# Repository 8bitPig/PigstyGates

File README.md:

# PigstyGates
teensy based USB-Midi to 24 Jack Gate Out

cc-by-nc-sa 4.0

v1:
Prototype failed! 
After about 2 weeks I stumbled upon the difference between the 74HC595 and 74HCT595.
Next Order will contain a 74HCT595 for retesting. 
Actually I have to guess, that the communication input levels are not enough for the 74HC595.
If this is not the Problem, I will retry with a line driver. 
v1 is still interesting for those who want a minimum part count and 0-5V Output levels. 
v1 code is still to do. Testcode is done and should work. To be shared after testing. 

v2:
-better layout
-correct part names and values
-got rid of SPI / using all 24 GPIO of the small size teensy boards
- TESTED AND WORKING :)
- ebay ADUM3160 USB Isolator since today was only working in theory. <- PROOVED!!!! :) 
- I sent in a sequence with 50% pulse cycle and 1/128 notes at a speed of 120 BPM in all 24 notes simultanously for testing without laggs on a teensy LC.
- code can't be simpler I guess. ^^

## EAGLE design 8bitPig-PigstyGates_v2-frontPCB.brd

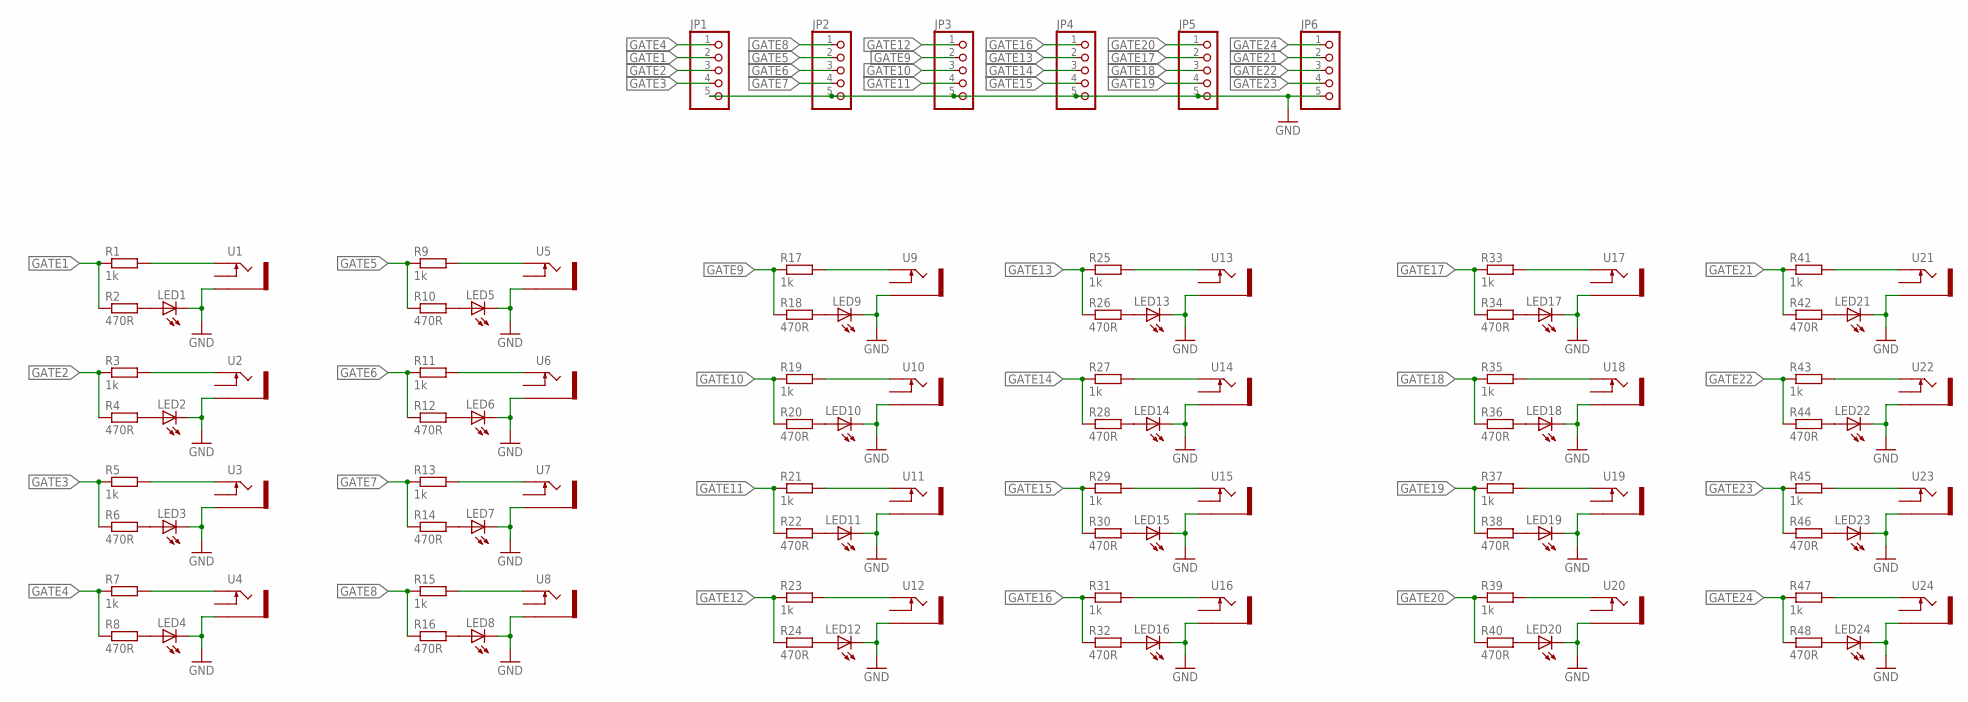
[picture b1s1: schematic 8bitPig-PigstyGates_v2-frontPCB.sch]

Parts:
JP1, JP2, JP3, JP4, JP5, JP6: PINHD-1X5; 1X05
LED1, LED2, LED3, LED4, LED5, LED6, LED7, LED8, LED9, LED10, LED11, LED12, LED13, LED14, LED15, LED16, LED17, LED18, LED19, LED20, LED21, LED22, LED23, LED24: LED3MM
R1, R3, R5, R7, R9, R11, R13, R15, R17, R19, R21, R23, R25, R27, R29, R31, R33, R35, R37, R39, R41, R43, R45, R47: 1k; R0603
R2, R4, R6, R8, R10, R12, R14, R16, R18, R20, R22, R24, R26, R28, R30, R32, R34, R36, R38, R40, R42, R44, R46, R48: 470R; R0603
U1, U2, U3, U4, U5, U6, U7, U8, U9, U10, U11, U12, U13, U14, U15, U16, U17, U18, U19, U20, U21, U22, U23, U24: THONKICONNNEW; WQP-PJ301M-12_JACK

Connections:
GATE1: JP1.2, R1.1, R2.1
GATE2: JP1.3, R3.1, R4.1
GATE3: JP1.4, R5.1, R6.1
GATE4: JP1.1, R7.1, R8.1
GATE5: JP2.2, R9.1, R10.1
GATE6: JP2.3, R11.1, R12.1
GATE7: JP2.4, R13.1, R14.1
GATE8: JP2.1, R15.1, R16.1
GATE9: JP3.2, R17.1, R18.1
GATE10: JP3.3, R19.1, R20.1
GATE11: JP3.4, R21.1, R22.1
GATE12: JP3.1, R23.1, R24.1
GATE13: JP4.2, R25.1, R26.1
GATE14: JP4.3, R27.1, R28.1
GATE15: JP4.4, R29.1, R30.1
GATE16: JP4.1, R31.1, R32.1
GATE17: JP5.2, R33.1, R34.1
GATE18: JP5.3, R35.1, R36.1
GATE19: JP5.4, R37.1, R38.1
GATE20: JP5.1, R39.1, R40.1
GATE21: JP6.2, R41.1, R42.1
GATE22: JP6.3, R43.1, R44.1
GATE23: JP6.4, R45.1, R46.1
GATE24: JP6.1, R47.1, R48.1
GND: JP1.5, JP2.5, JP3.5, JP4.5, JP5.5, JP6.5, LED1.K (C), LED2.K (C), LED3.K (C), LED4.K (C), LED5.K (C), LED6.K (C), LED7.K (C), LED8.K (C), LED9.K (C), LED10.K (C), LED11.K (C), LED12.K (C), LED13.K (C), LED14.K (C), LED15.K (C), LED16.K (C), LED17.K (C), LED18.K (C), LED19.K (C), LED20.K (C), LED21.K (C), LED22.K (C), LED23.K (C), LED24.K (C), U1.P$3_SLEEVE (SLEEVE), U2.P$3_SLEEVE (SLEEVE), U3.P$3_SLEEVE (SLEEVE), U4.P$3_SLEEVE (SLEEVE), U5.P$3_SLEEVE (SLEEVE), U6.P$3_SLEEVE (SLEEVE), U7.P$3_SLEEVE (SLEEVE), U8.P$3_SLEEVE (SLEEVE), U9.P$3_SLEEVE (SLEEVE), U10.P$3_SLEEVE (SLEEVE), U11.P$3_SLEEVE (SLEEVE), U12.P$3_SLEEVE (SLEEVE), U13.P$3_SLEEVE (SLEEVE), U14.P$3_SLEEVE (SLEEVE), U15.P$3_SLEEVE (SLEEVE), U16.P$3_SLEEVE (SLEEVE), U17.P$3_SLEEVE (SLEEVE), U18.P$3_SLEEVE (SLEEVE), U19.P$3_SLEEVE (SLEEVE), U20.P$3_SLEEVE (SLEEVE), U21.P$3_SLEEVE (SLEEVE), U22.P$3_SLEEVE (SLEEVE), U23.P$3_SLEEVE (SLEEVE), U24.P$3_SLEEVE (SLEEVE)
unnamed: LED1.A, R2.2
unnamed: R1.2, U1.P$1_TIP (TIP)
unnamed: LED2.A, R4.2
unnamed: R3.2, U2.P$1_TIP (TIP)
unnamed: LED3.A, R6.2
unnamed: R5.2, U3.P$1_TIP (TIP)
unnamed: LED4.A, R8.2
unnamed: R7.2, U4.P$1_TIP (TIP)
unnamed: LED5.A, R10.2
unnamed: R9.2, U5.P$1_TIP (TIP)
unnamed: LED6.A, R12.2
unnamed: R11.2, U6.P$1_TIP (TIP)
unnamed: LED7.A, R14.2
unnamed: R13.2, U7.P$1_TIP (TIP)
unnamed: LED8.A, R16.2
unnamed: R15.2, U8.P$1_TIP (TIP)
unnamed: LED9.A, R18.2
unnamed: R17.2, U9.P$1_TIP (TIP)
unnamed: LED10.A, R20.2
unnamed: R19.2, U10.P$1_TIP (TIP)
unnamed: LED11.A, R22.2
unnamed: R21.2, U11.P$1_TIP (TIP)
unnamed: LED12.A, R24.2
unnamed: R23.2, U12.P$1_TIP (TIP)
unnamed: LED13.A, R26.2
unnamed: R25.2, U13.P$1_TIP (TIP)
unnamed: LED14.A, R28.2
unnamed: R27.2, U14.P$1_TIP (TIP)
unnamed: LED15.A, R30.2
unnamed: R29.2, U15.P$1_TIP (TIP)
unnamed: LED17.A, R34.2
unnamed: R33.2, U17.P$1_TIP (TIP)
unnamed: LED16.A, R32.2
unnamed: R31.2, U16.P$1_TIP (TIP)
unnamed: LED18.A, R36.2
unnamed: R35.2, U18.P$1_TIP (TIP)
unnamed: LED19.A, R38.2
unnamed: R37.2, U19.P$1_TIP (TIP)
unnamed: LED20.A, R40.2
unnamed: R39.2, U20.P$1_TIP (TIP)
unnamed: LED21.A, R42.2
unnamed: R41.2, U21.P$1_TIP (TIP)
unnamed: LED22.A, R44.2
unnamed: R43.2, U22.P$1_TIP (TIP)
unnamed: LED23.A, R46.2
unnamed: R45.2, U23.P$1_TIP (TIP)
unnamed: LED24.A, R48.2
unnamed: R47.2, U24.P$1_TIP (TIP)

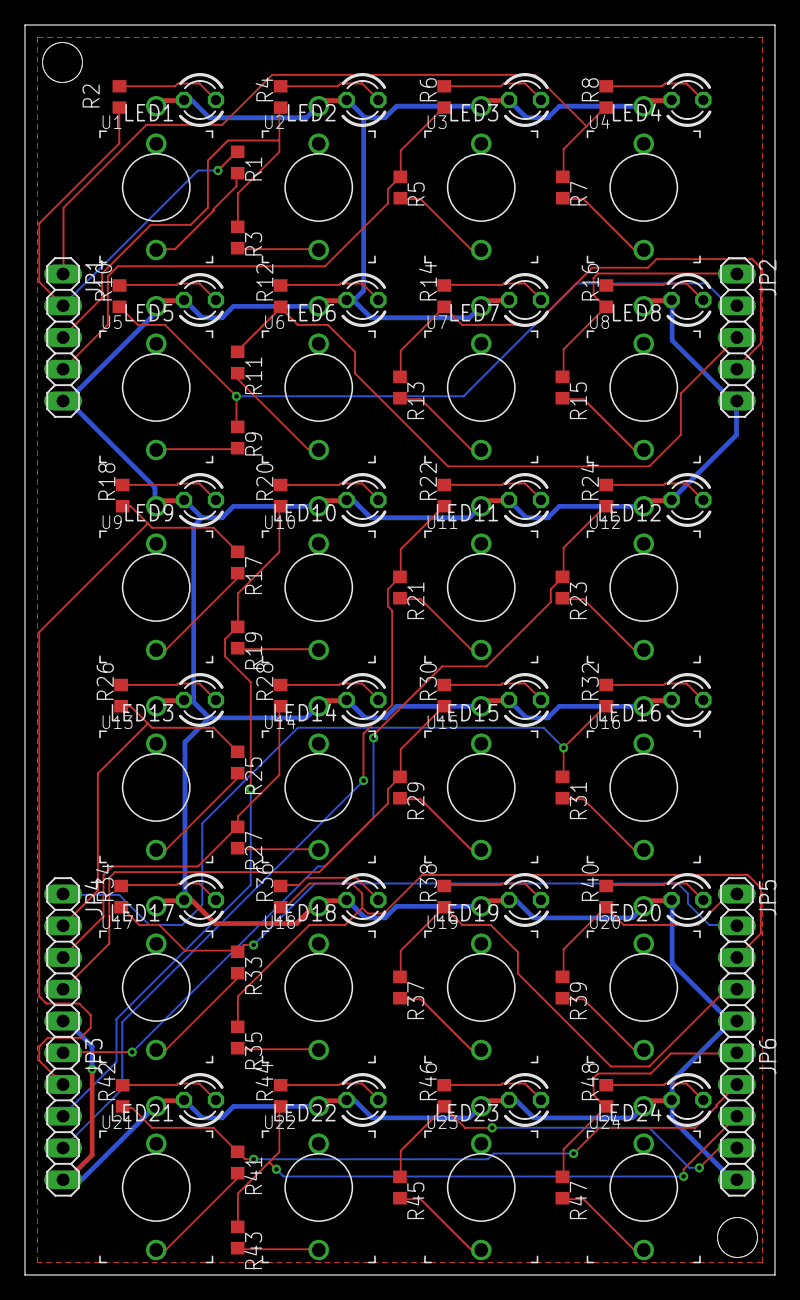
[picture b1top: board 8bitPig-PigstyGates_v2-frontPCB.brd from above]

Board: 2 copper layers, 60.0 x 100.0 mm, 102 parts (0 on the bottom side), 73 nets.

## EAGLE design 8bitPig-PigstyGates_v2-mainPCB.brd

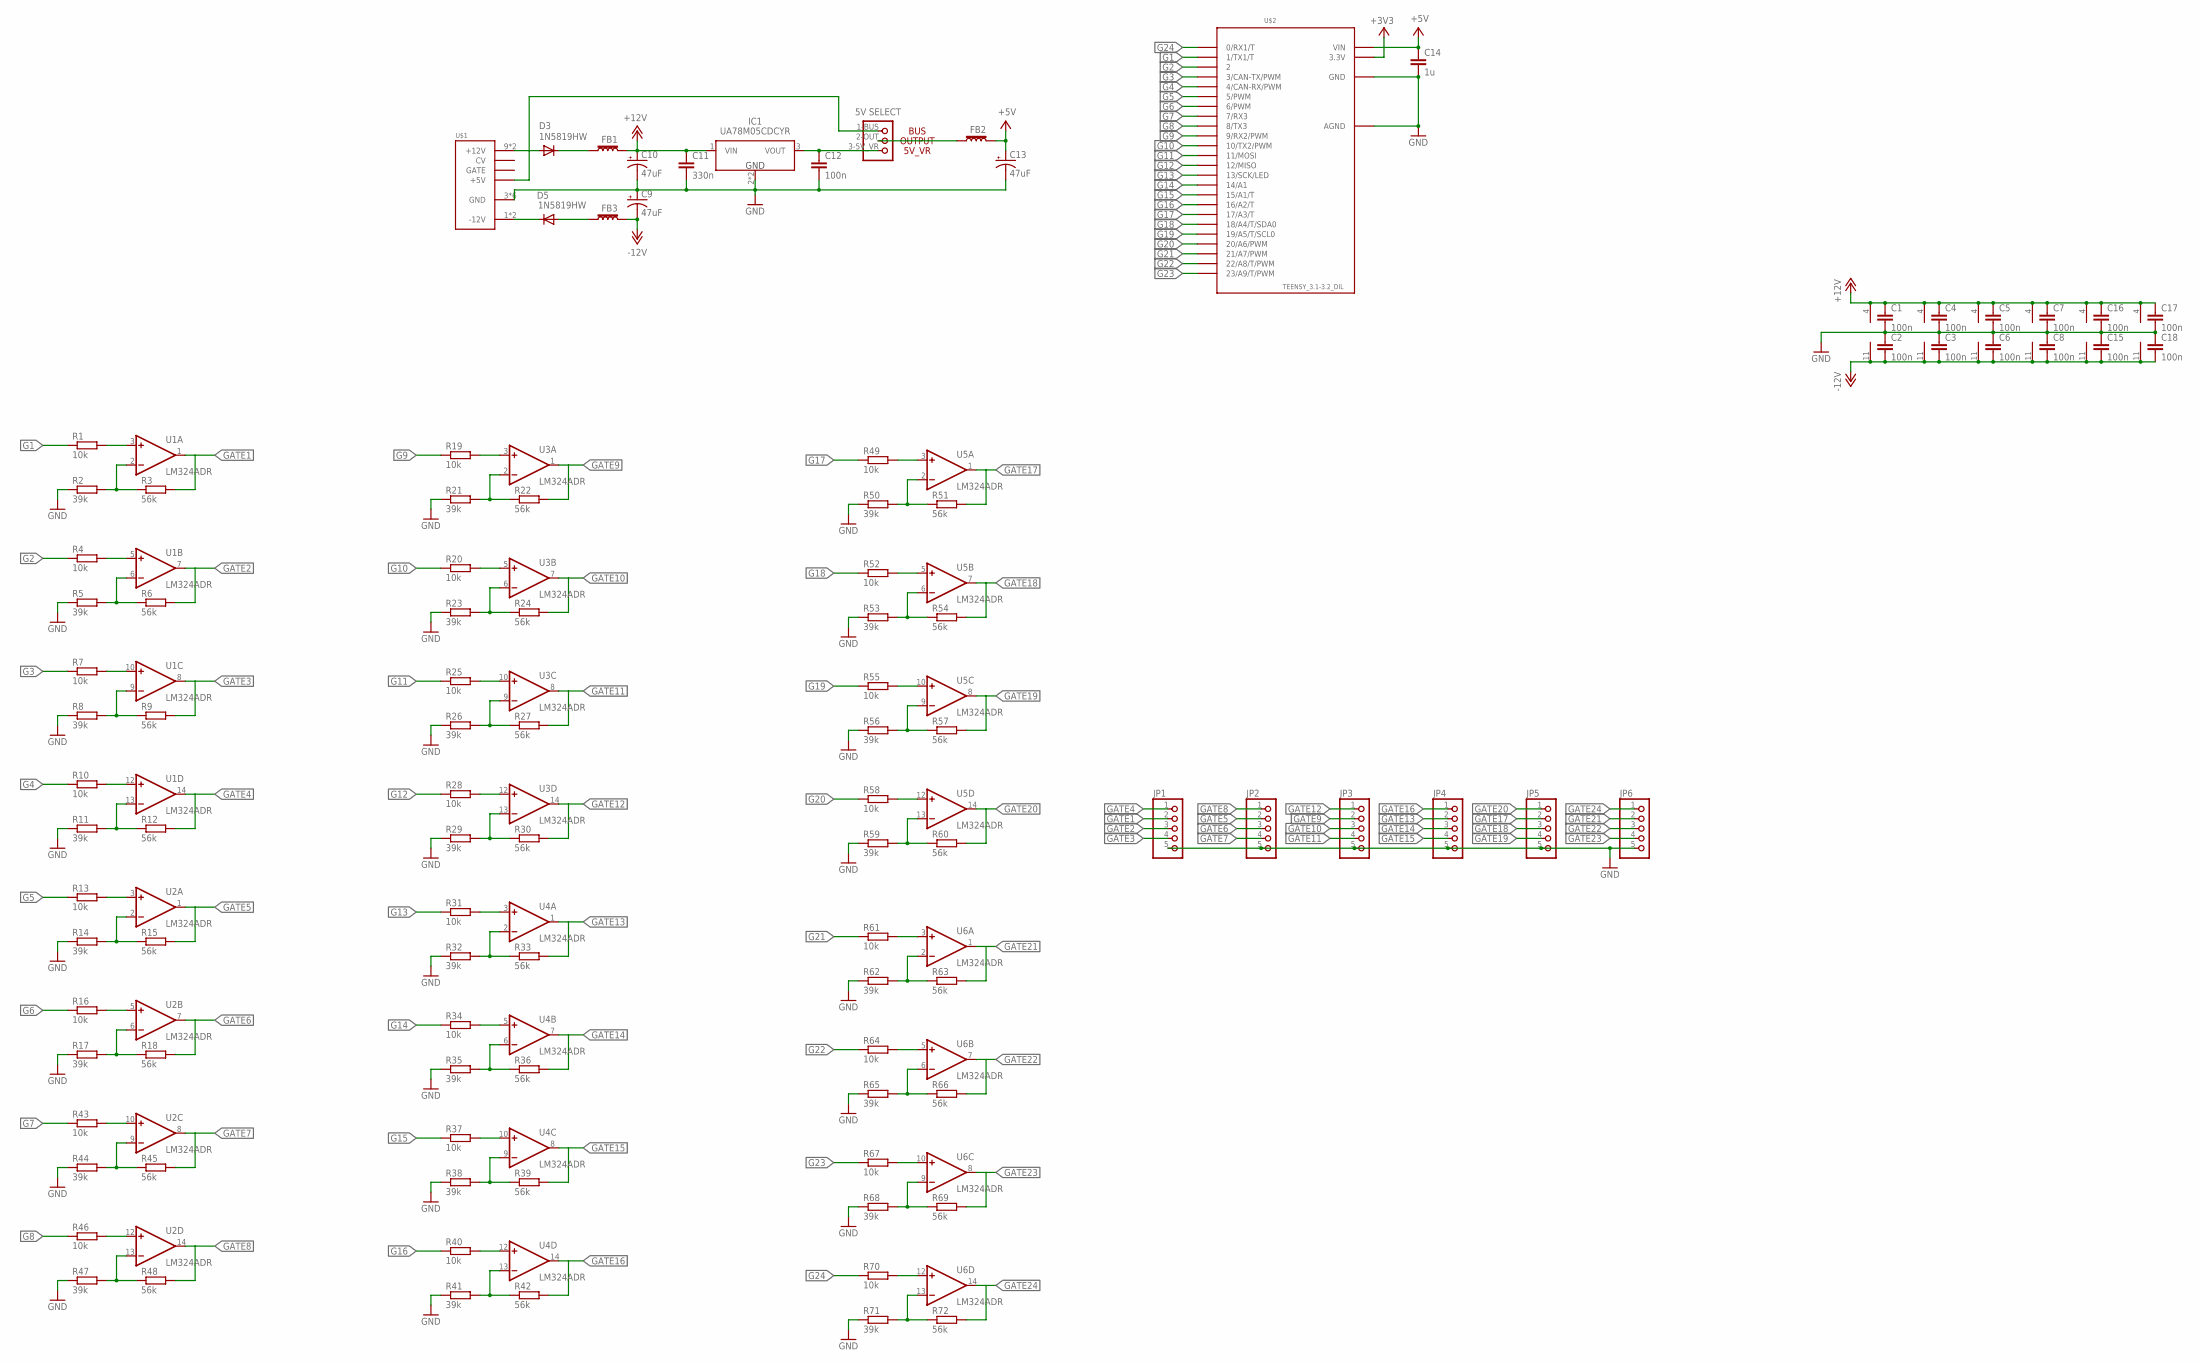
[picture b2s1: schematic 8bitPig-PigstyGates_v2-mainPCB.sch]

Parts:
C1, C2, C3, C4, C5, C6, C7, C8, C12, C15, C16, C17, C18: 100n; C0603
C9, C10, C13: 47uF; PANASONIC_D
C11: 330n; C0603
C14: 1u; C0603
D3, D5: 1N5819HW; DIODE_SOD123
FB1, FB2, FB3: 30Ω/1.8A; 0603
IC1: UA78M05CDCYR; SOT230P700X180-4N
JP1, JP2, JP3, JP4, JP5, JP6: PINHD-1X5; 1X05
JP_5V: SELECTOR_POWER
R1, R4, R7, R10, R13, R16, R19, R20, R25, R28, R31, R34, R37, R40, R43, R46, R49, R52, R55, R58, R61, R64, R67, R70: 10k; R0603
R2, R5, R8, R11, R14, R17, R21, R23, R26, R29, R32, R35, R38, R41, R44, R47, R50, R53, R56, R59, R62, R65, R68, R71: 39k; R0603
R3, R6, R9, R12, R15, R18, R22, R24, R27, R30, R33, R36, R39, R42, R45, R48, R51, R54, R57, R60, R63, R66, R69, R72: 56k; R0603
U1, U2, U3, U4, U5, U6: LM324ADR; SO14
U$1: POWER; POWER_16
U$2: TEENSY_3.1-3.2_DIL; TEENSY_3.0-3.2&LC_DIL

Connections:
+3V3: U$2.3.3V
+5V: C13.+, C14.1, FB2.2, U$2.VIN
+12V: C1.1, C4.1, C5.1, C7.1, C10.+, C11.1, C16.1, C17.1, FB1.2, IC1.1 (VIN), U1.4 (V+), U2.4 (V+), U3.4 (V+), U4.4 (V+), U5.4 (V+), U6.4 (V+)
-12V: C2.2, C3.2, C6.2, C8.2, C9.-, C15.2, C18.2, FB3.2, U1.11 (V-), U2.11 (V-), U3.11 (V-), U4.11 (V-), U5.11 (V-), U6.11 (V-)
G1: R1.1, U$2.1 (1/TX1/T)
G2: R4.1, U$2.2
G3: R7.1, U$2.3 (3/CAN-TX/PWM)
G4: R10.1, U$2.4 (4/CAN-RX/PWM)
G5: R13.1, U$2.5 (5/PWM)
G6: R16.1, U$2.6 (6/PWM)
G7: R43.1, U$2.7 (7/RX3)
G8: R46.1, U$2.8 (8/TX3)
G9: R19.1, U$2.9 (9/RX2/PWM)
G10: R20.1, U$2.10 (10/TX2/PWM)
G11: R25.1, U$2.11 (11/MOSI)
G12: R28.1, U$2.12 (12/MISO)
G13: R31.1, U$2.13 (13/SCK/LED)
G14: R34.1, U$2.14/A0 (14/A1)
G15: R37.1, U$2.15/A1 (15/A1/T)
G16: R40.1, U$2.16/A2 (16/A2/T)
G17: R49.1, U$2.17/A3 (17/A3/T)
G18: R52.1, U$2.18/A4 (18/A4/T/SDA0)
G19: R55.1, U$2.19/A5 (19/A5/T/SCL0)
G20: R58.1, U$2.20/A6 (20/A6/PWM)
G21: R61.1, U$2.21/A7 (21/A7/PWM)
G22: R64.1, U$2.22/A8 (22/A8/T/PWM)
G23: R67.1, U$2.23/A9 (23/A9/T/PWM)
G24: R70.1, U$2.0 (0/RX1/T)
GATE1: JP1.2, R3.2, U1.1 (OUT)
GATE2: JP1.3, R6.2, U1.7 (OUT)
GATE3: JP1.4, R9.2, U1.8 (OUT)
GATE4: JP1.1, R12.2, U1.14 (OUT)
GATE5: JP2.2, R15.2, U2.1 (OUT)
GATE6: JP2.3, R18.2, U2.7 (OUT)
GATE7: JP2.4, R45.2, U2.8 (OUT)
GATE8: JP2.1, R48.2, U2.14 (OUT)
GATE9: JP3.2, R22.2, U3.1 (OUT)
GATE10: JP3.3, R24.2, U3.7 (OUT)
GATE11: JP3.4, R27.2, U3.8 (OUT)
GATE12: JP3.1, R30.2, U3.14 (OUT)
GATE13: JP4.2, R33.2, U4.1 (OUT)
GATE14: JP4.3, R36.2, U4.7 (OUT)
GATE15: JP4.4, R39.2, U4.8 (OUT)
GATE16: JP4.1, R42.2, U4.14 (OUT)
GATE17: JP5.2, R51.2, U5.1 (OUT)
GATE18: JP5.3, R54.2, U5.7 (OUT)
GATE19: JP5.4, R57.2, U5.8 (OUT)
GATE20: JP5.1, R60.2, U5.14 (OUT)
GATE21: JP6.2, R63.2, U6.1 (OUT)
GATE22: JP6.3, R66.2, U6.7 (OUT)
GATE23: JP6.4, R69.2, U6.8 (OUT)
GATE24: JP6.1, R72.2, U6.14 (OUT)
GND: C1.2, C2.1, C3.1, C4.2, C5.2, C6.1, C7.2, C8.1, C9.+, C10.-, C11.2, C12.2, C13.-, C14.2, C15.1, C16.2, C17.2, C18.1, IC1.2 (GND), IC1.4 (GND), JP1.5, JP2.5, JP3.5, JP4.5, JP5.5, JP6.5, R2.1, R5.1, R8.1, R11.1, R14.1, R17.1, R21.1, R23.1, R26.1, R29.1, R32.1, R35.1, R38.1, R41.1, R44.1, R47.1, R50.1, R53.1, R56.1, R59.1, R62.1, R65.1, R68.1, R71.1, U$1.3 (GND), U$1.4 (GND), U$1.5 (GND), U$1.6 (GND), U$1.7 (GND), U$1.8 (GND), U$2.AGND, U$2.GND
unnamed: R1.2, U1.3 (+IN)
unnamed: R2.2, R3.1, U1.2 (-IN)
unnamed: R4.2, U1.5 (+IN)
unnamed: R5.2, R6.1, U1.6 (-IN)
unnamed: R7.2, U1.10 (+IN)
unnamed: R8.2, R9.1, U1.9 (-IN)
unnamed: R10.2, U1.12 (+IN)
unnamed: R11.2, R12.1, U1.13 (-IN)
unnamed: D3.A, U$1.9 (+12V), U$1.10 (+12V)
unnamed: D5.C, U$1.1 (-12V), U$1.2 (-12V)
unnamed: D5.A, FB3.1
unnamed: D3.C, FB1.1
unnamed: JP_5V.1-BUS, U$1.11 (+5V), U$1.12 (+5V)
unnamed: C12.1, IC1.3 (VOUT), JP_5V.3-5V_VR (3-VR)
unnamed: FB2.1, JP_5V.2-OUT
unnamed: R13.2, U2.3 (+IN)
unnamed: R19.2, U3.3 (+IN)
unnamed: R20.2, U3.5 (+IN)
unnamed: R21.2, R22.1, U3.2 (-IN)
unnamed: R23.2, R24.1, U3.6 (-IN)
unnamed: R25.2, U3.10 (+IN)
unnamed: R26.2, R27.1, U3.9 (-IN)
unnamed: R28.2, U3.12 (+IN)
unnamed: R29.2, R30.1, U3.13 (-IN)
unnamed: R31.2, U4.3 (+IN)
unnamed: R32.2, R33.1, U4.2 (-IN)
unnamed: R34.2, U4.5 (+IN)
unnamed: R35.2, R36.1, U4.6 (-IN)
unnamed: R37.2, U4.10 (+IN)
unnamed: R38.2, R39.1, U4.9 (-IN)
unnamed: R40.2, U4.12 (+IN)
unnamed: R41.2, R42.1, U4.13 (-IN)
unnamed: R14.2, R15.1, U2.2 (-IN)
unnamed: R16.2, U2.5 (+IN)
unnamed: R17.2, R18.1, U2.6 (-IN)
unnamed: R43.2, U2.10 (+IN)
unnamed: R44.2, R45.1, U2.9 (-IN)
unnamed: R46.2, U2.12 (+IN)
unnamed: R47.2, R48.1, U2.13 (-IN)
unnamed: R49.2, U5.3 (+IN)
unnamed: R50.2, R51.1, U5.2 (-IN)
unnamed: R52.2, U5.5 (+IN)
unnamed: R53.2, R54.1, U5.6 (-IN)
unnamed: R55.2, U5.10 (+IN)
unnamed: R56.2, R57.1, U5.9 (-IN)
unnamed: R58.2, U5.12 (+IN)
unnamed: R59.2, R60.1, U5.13 (-IN)
unnamed: R61.2, U6.3 (+IN)
unnamed: R62.2, R63.1, U6.2 (-IN)
unnamed: R64.2, U6.5 (+IN)
unnamed: R65.2, R66.1, U6.6 (-IN)
unnamed: R67.2, U6.10 (+IN)
unnamed: R68.2, R69.1, U6.9 (-IN)
unnamed: R70.2, U6.12 (+IN)
unnamed: R71.2, R72.1, U6.13 (-IN)

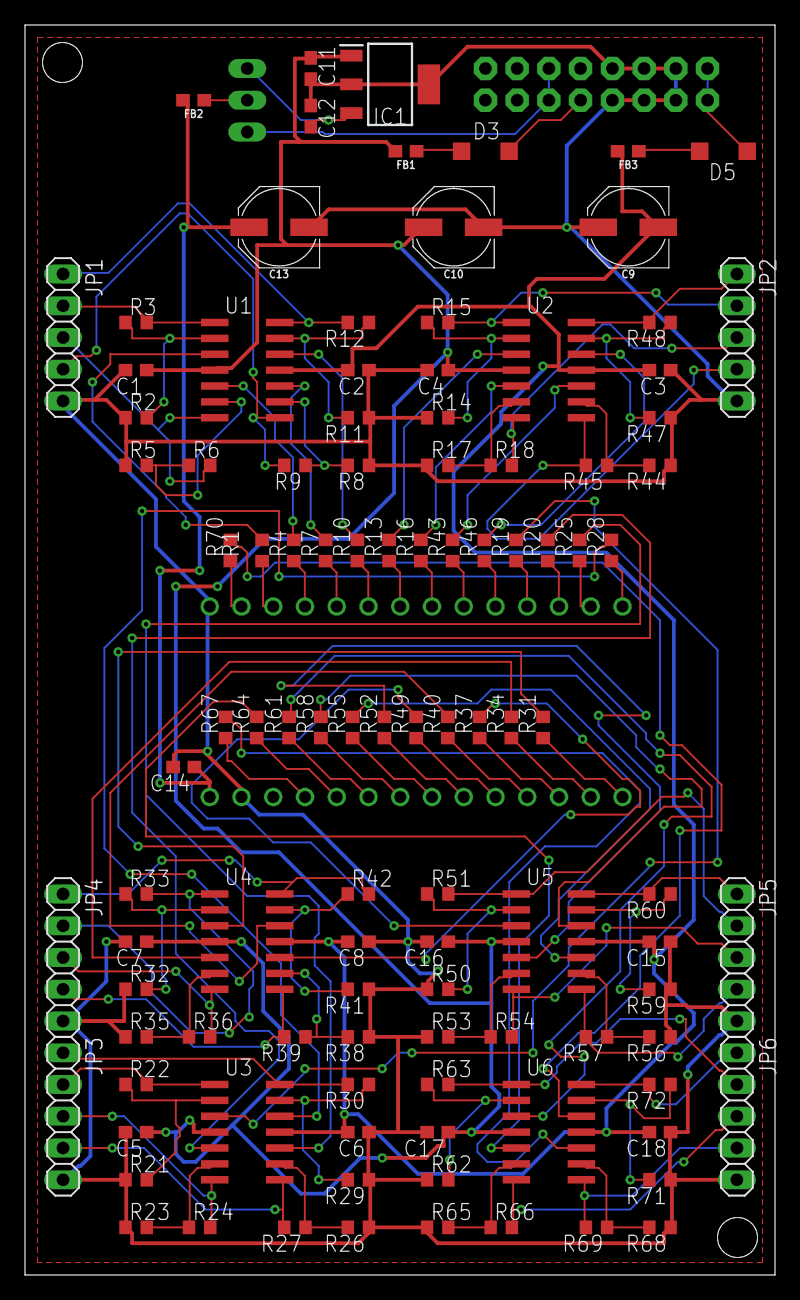
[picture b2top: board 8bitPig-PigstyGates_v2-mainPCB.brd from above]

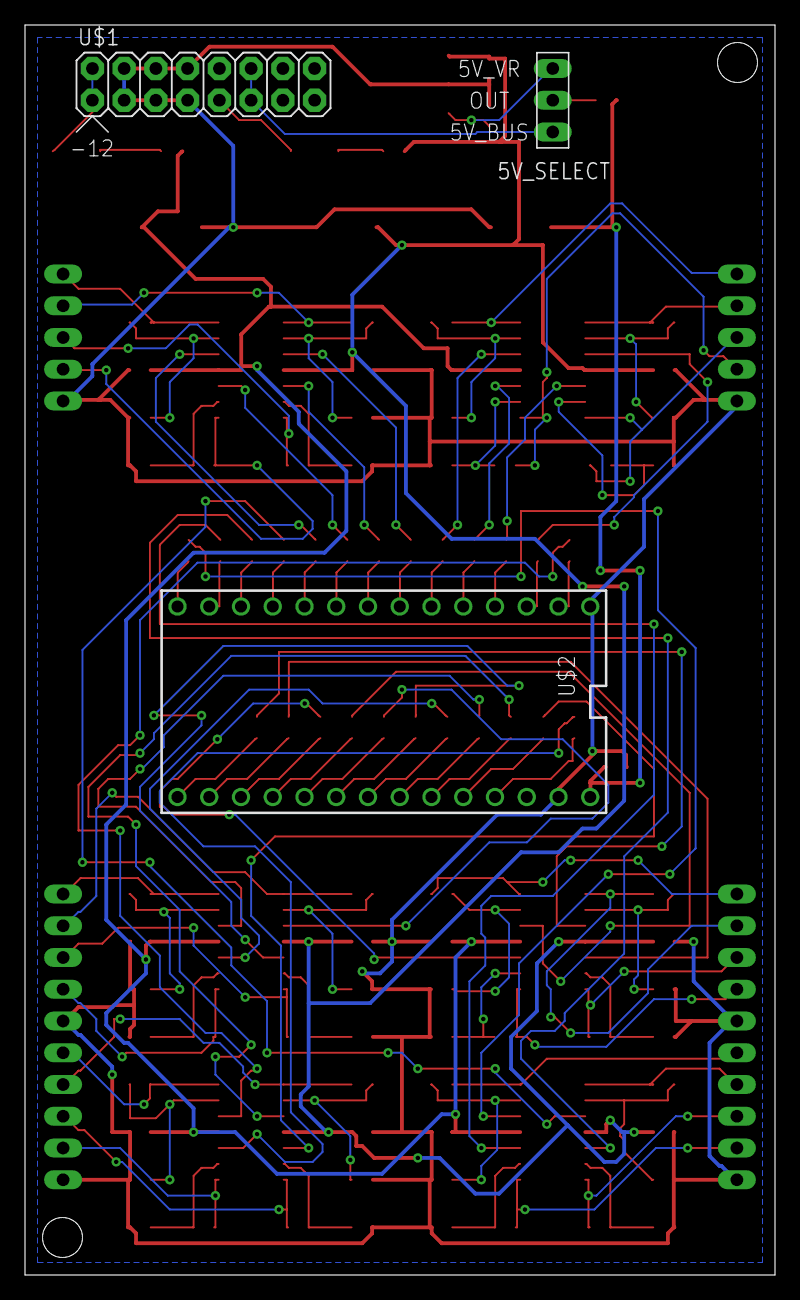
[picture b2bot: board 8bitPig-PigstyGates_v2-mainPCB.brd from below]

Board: 2 copper layers, 60.0 x 100.0 mm, 111 parts (3 on the bottom side), 107 nets.

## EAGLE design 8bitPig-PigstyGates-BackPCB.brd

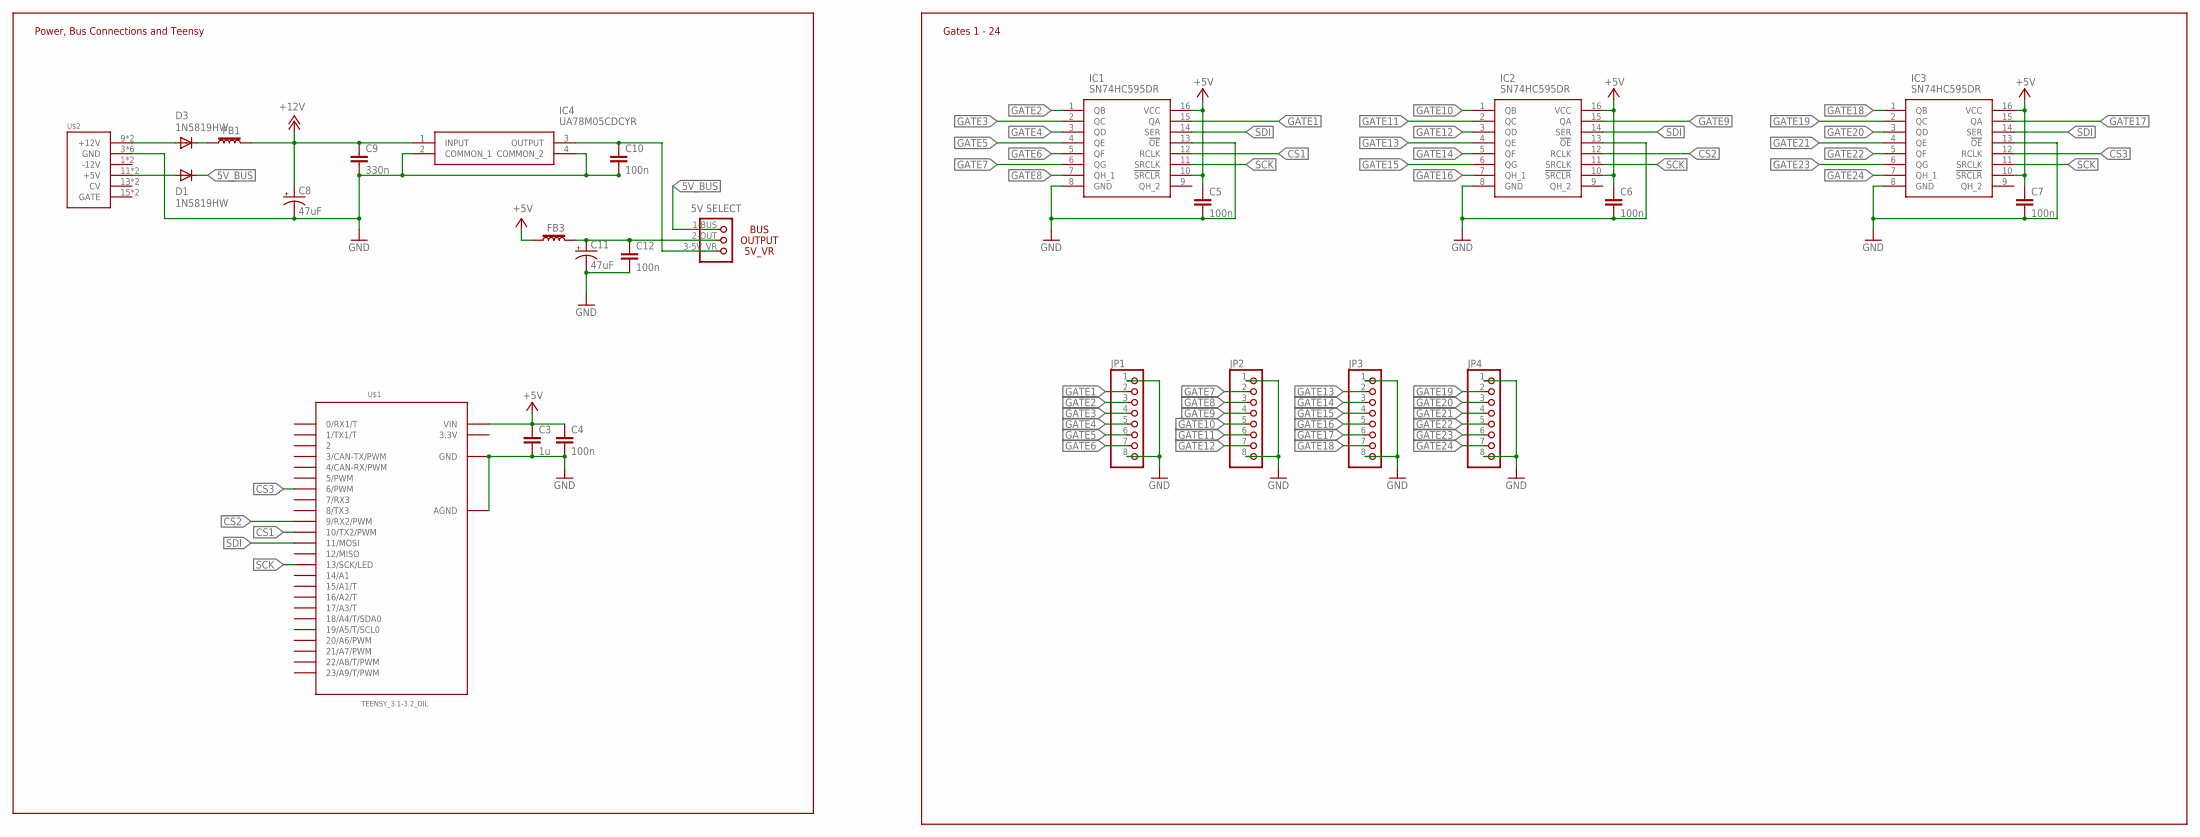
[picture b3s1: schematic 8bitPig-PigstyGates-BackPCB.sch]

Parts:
C3: 1u; C0603
C4, C5, C6, C7, C10, C12: 100n; C0603
C8, C11: 47uF; PANASONIC_D
C9: 330n; C0603
D1, D3: 1N5819HW; DIODE_SOD123
FB1, FB3: 30Ω/1.8A; 0603
IC1, IC2, IC3: SN74HC595DR; SOIC127P600X175-16N
IC4: UA78M05CDCYR; SOT230P700X180-4N
JP1, JP2, JP3, JP4: PINHD-1X8; 1X08
JP5: SELECTOR_POWER
U$1: TEENSY_3.1-3.2_DIL; TEENSY_3.0-3.2&LC_DIL
U$2: POWER; POWER_16

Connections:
3.3V: U$1.3.3V
5V_BUS: D1.C, JP5.1-BUS
+5V: C3.1, C4.1, C5.1, C6.1, C7.1, FB3.1, IC1.10 (!SRCLR), IC1.16 (VCC), IC2.10 (!SRCLR), IC2.16 (VCC), IC3.10 (!SRCLR), IC3.16 (VCC), U$1.VIN
+12V: C8.+, C9.1, FB1.2, IC4.1 (INPUT)
CS1: IC1.12 (RCLK), U$1.10 (10/TX2/PWM)
CS2: IC2.12 (RCLK), U$1.9 (9/RX2/PWM)
CS3: IC3.12 (RCLK), U$1.6 (6/PWM)
GATE1: IC1.15 (QA), JP1.2
GATE2: IC1.1 (QB), JP1.3
GATE3: IC1.2 (QC), JP1.4
GATE4: IC1.3 (QD), JP1.5
GATE5: IC1.4 (QE), JP1.6
GATE6: IC1.5 (QF), JP1.7
GATE7: IC1.6 (QG), JP2.2
GATE8: IC1.7 (QH_1), JP2.3
GATE9: IC2.15 (QA), JP2.4
GATE10: IC2.1 (QB), JP2.5
GATE11: IC2.2 (QC), JP2.6
GATE12: IC2.3 (QD), JP2.7
GATE13: IC2.4 (QE), JP3.2
GATE14: IC2.5 (QF), JP3.3
GATE15: IC2.6 (QG), JP3.4
GATE16: IC2.7 (QH_1), JP3.5
GATE17: IC3.15 (QA), JP3.6
GATE18: IC3.1 (QB), JP3.7
GATE19: IC3.2 (QC), JP4.2
GATE20: IC3.3 (QD), JP4.3
GATE21: IC3.4 (QE), JP4.4
GATE22: IC3.5 (QF), JP4.5
GATE23: IC3.6 (QG), JP4.6
GATE24: IC3.7 (QH_1), JP4.7
GND: C3.2, C4.2, C5.2, C6.2, C7.2, C8.-, C9.2, C10.2, C11.-, C12.2, IC1.8 (GND), IC1.13 (!OE), IC2.8 (GND), IC2.13 (!OE), IC3.8 (GND), IC3.13 (!OE), IC4.2 (COMMON_1), IC4.4 (COMMON_2), JP1.1, JP1.8, JP2.1, JP2.8, JP3.1, JP3.8, JP4.1, JP4.8, U$1.AGND, U$1.GND, U$2.3 (GND), U$2.4 (GND), U$2.5 (GND), U$2.6 (GND), U$2.7 (GND), U$2.8 (GND)
unnamed: D3.A, U$2.9 (+12V), U$2.10 (+12V)
unnamed: D1.A, U$2.11 (+5V), U$2.12 (+5V)
unnamed: C11.+, C12.1, FB3.2, JP5.2-OUT
unnamed: D3.C, FB1.1
unnamed: C10.1, IC4.3 (OUTPUT), JP5.3-5V_VR (3-VR)
SCK: IC1.11 (SRCLK), IC2.11 (SRCLK), IC3.11 (SRCLK), U$1.13 (13/SCK/LED)
SDI: IC1.14 (SER), IC2.14 (SER), IC3.14 (SER), U$1.11 (11/MOSI)

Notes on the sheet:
Gates 1 - 24
Power, Bus Connections and Teensy

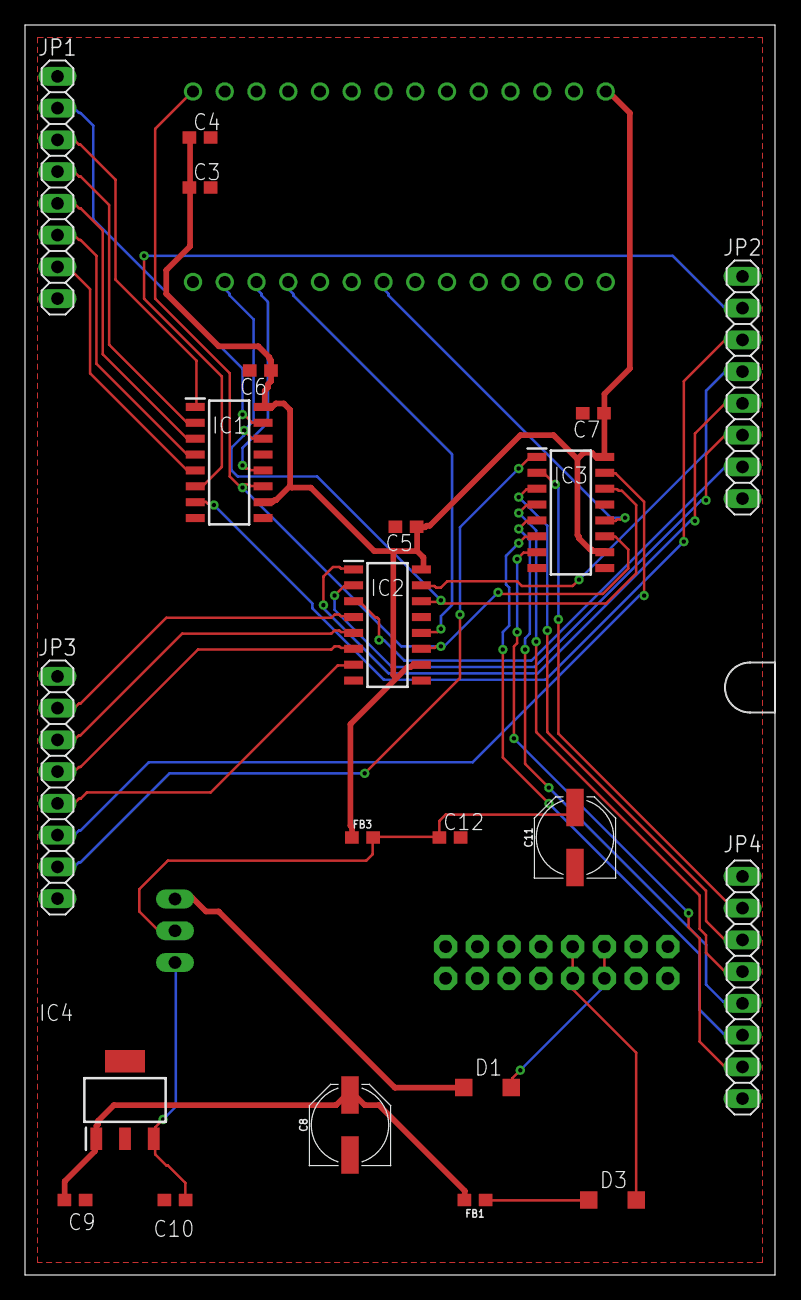
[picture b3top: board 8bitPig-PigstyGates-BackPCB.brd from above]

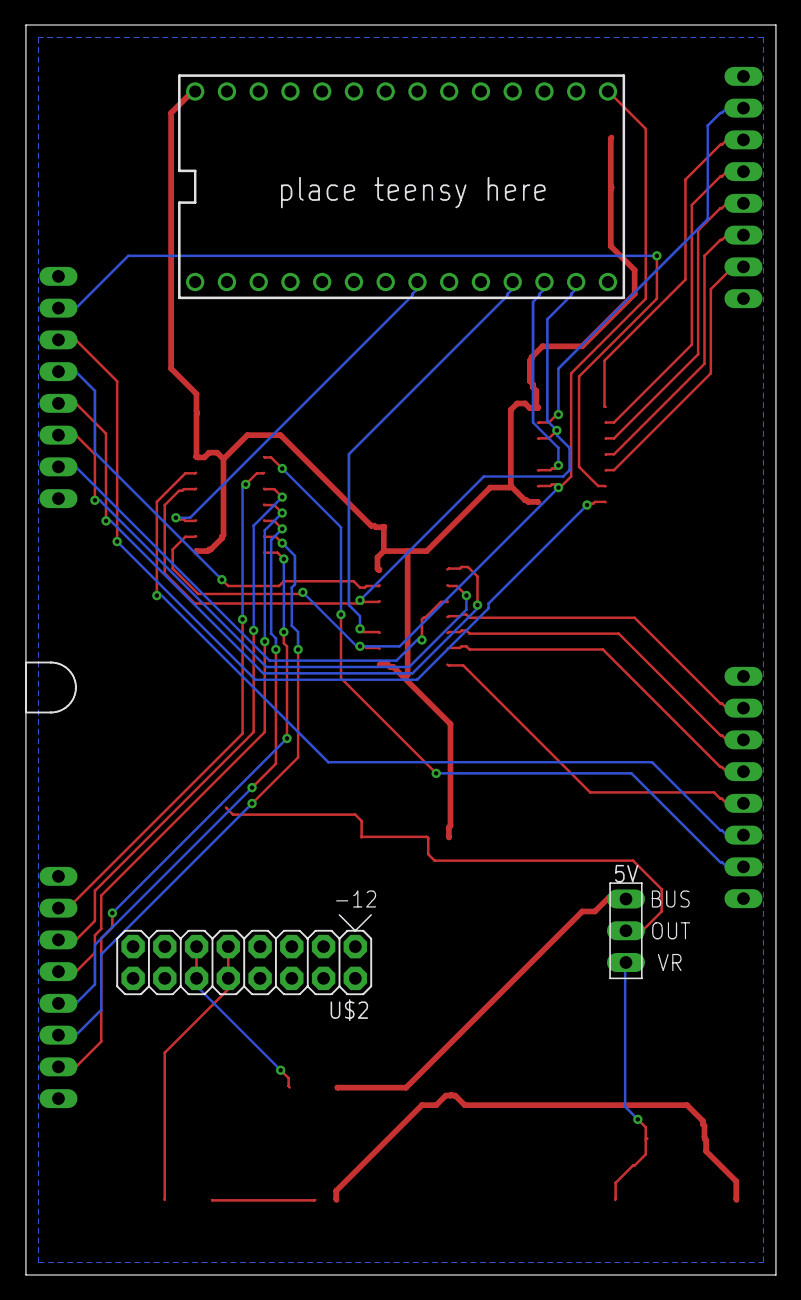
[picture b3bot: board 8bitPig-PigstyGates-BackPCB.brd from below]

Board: 2 copper layers, 59.9 x 99.8 mm, 26 parts (3 on the bottom side), 38 nets.

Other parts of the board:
U$3: PANEL_CABLE_CUTOUT

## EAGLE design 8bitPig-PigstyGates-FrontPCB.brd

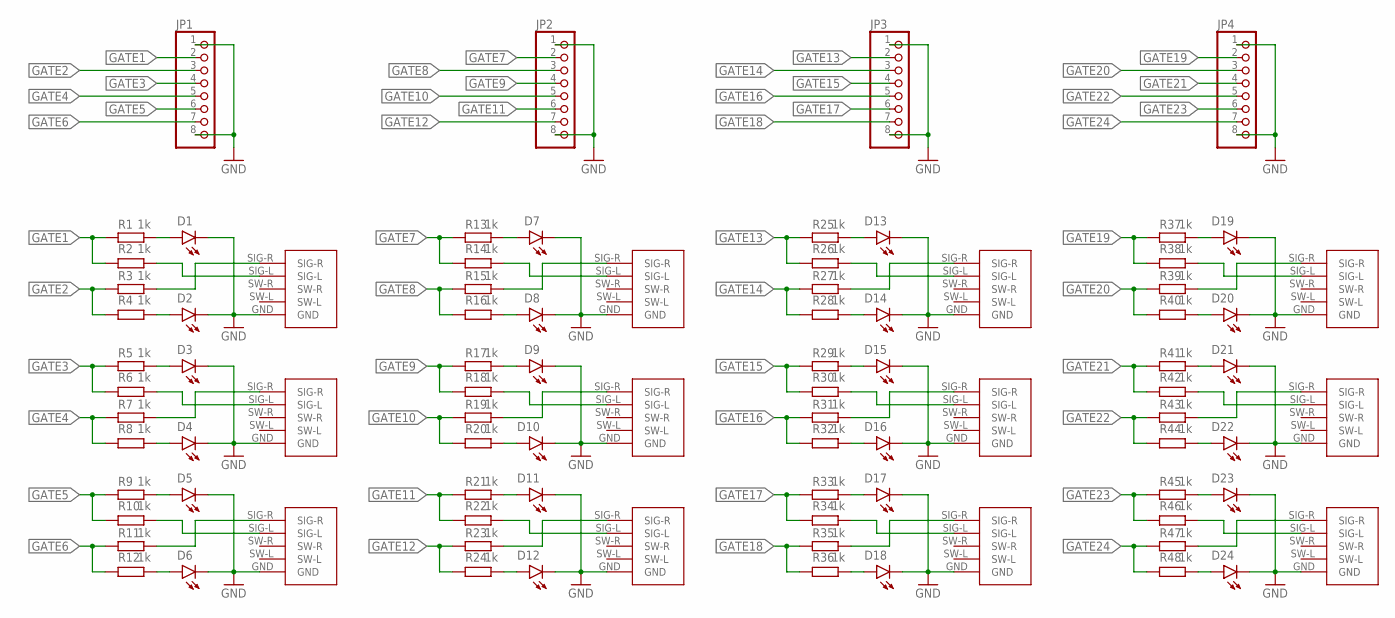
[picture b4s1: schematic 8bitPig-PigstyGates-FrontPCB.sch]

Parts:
D1, D2, D3, D4, D5, D6, D7, D8, D9, D10, D11, D12, D13, D14, D15, D16, D17, D18, D19, D20, D21, D22, D23, D24: LED3MM; LED_3MM
DUAL_JACK_1, DUAL_JACK_2, DUAL_JACK_3, DUAL_JACK_4, DUAL_JACK_5, DUAL_JACK_6, DUAL_JACK_7, DUAL_JACK_8, DUAL_JACK_9, DUAL_JACK_10, DUAL_JACK_11, DUAL_JACK_12: DUAL_MONO_THONKICONN; DUAL_THONKICONN_MONO
JP1, JP2, JP3, JP4: PINHD-1X8; 1X08
R1, R2, R3, R4, R5, R6, R7, R8, R9, R10, R11, R12, R13, R14, R15, R16, R17, R18, R19, R20, R21, R22, R23, R24, R25, R26, R27, R28, R29, R30, R31, R32, R33, R34, R35, R36, R37, R38, R39, R40, R41, R42, R43, R44, R45, R46, R47, R48: 1k; R0603

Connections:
GATE1: JP1.2, R1.1, R2.1
GATE2: JP1.3, R3.1, R4.1
GATE3: JP1.4, R5.1, R6.1
GATE4: JP1.5, R7.1, R8.1
GATE5: JP1.6, R9.1, R10.1
GATE6: JP1.7, R11.1, R12.1
GATE7: JP2.2, R13.1, R14.1
GATE8: JP2.3, R15.1, R16.1
GATE9: JP2.4, R17.1, R18.1
GATE10: JP2.5, R19.1, R20.1
GATE11: JP2.6, R21.1, R22.1
GATE12: JP2.7, R23.1, R24.1
GATE13: JP3.2, R25.1, R26.1
GATE14: JP3.3, R27.1, R28.1
GATE15: JP3.4, R29.1, R30.1
GATE16: JP3.5, R31.1, R32.1
GATE17: JP3.6, R33.1, R34.1
GATE18: JP3.7, R35.1, R36.1
GATE19: JP4.2, R37.1, R38.1
GATE20: JP4.3, R39.1, R40.1
GATE21: JP4.4, R41.1, R42.1
GATE22: JP4.5, R43.1, R44.1
GATE23: JP4.6, R45.1, R46.1
GATE24: JP4.7, R47.1, R48.1
GND: D1.K (C), D2.K (C), D3.K (C), D4.K (C), D5.K (C), D6.K (C), D7.K (C), D8.K (C), D9.K (C), D10.K (C), D11.K (C), D12.K (C), D13.K (C), D14.K (C), D15.K (C), D16.K (C), D17.K (C), D18.K (C), D19.K (C), D20.K (C), D21.K (C), D22.K (C), D23.K (C), D24.K (C), DUAL_JACK_1.GND, DUAL_JACK_2.GND, DUAL_JACK_3.GND, DUAL_JACK_4.GND, DUAL_JACK_5.GND, DUAL_JACK_6.GND, DUAL_JACK_7.GND, DUAL_JACK_8.GND, DUAL_JACK_9.GND, DUAL_JACK_10.GND, DUAL_JACK_11.GND, DUAL_JACK_12.GND, JP1.1, JP1.8, JP2.1, JP2.8, JP3.1, JP3.8, JP4.1, JP4.8
unnamed: DUAL_JACK_2.SIG-R, R7.2
unnamed: DUAL_JACK_1.SIG-L, R2.2
unnamed: D4.A, R8.2
unnamed: D3.A, R5.2
unnamed: D1.A, R1.2
unnamed: DUAL_JACK_2.SIG-L, R6.2
unnamed: DUAL_JACK_3.SIG-R, R11.2
unnamed: D6.A, R12.2
unnamed: D5.A, R9.2
unnamed: DUAL_JACK_3.SIG-L, R10.2
unnamed: DUAL_JACK_4.SIG-R, R15.2
unnamed: D8.A, R16.2
unnamed: D7.A, R13.2
unnamed: DUAL_JACK_4.SIG-L, R14.2
unnamed: DUAL_JACK_5.SIG-R, R19.2
unnamed: D10.A, R20.2
unnamed: DUAL_JACK_1.SIG-R, R3.2
unnamed: D9.A, R17.2
unnamed: DUAL_JACK_5.SIG-L, R18.2
unnamed: DUAL_JACK_6.SIG-R, R23.2
unnamed: D2.A, R4.2
unnamed: D12.A, R24.2
unnamed: D11.A, R21.2
unnamed: DUAL_JACK_6.SIG-L, R22.2
unnamed: DUAL_JACK_7.SIG-R, R27.2
unnamed: D14.A, R28.2
unnamed: D13.A, R25.2
unnamed: DUAL_JACK_7.SIG-L, R26.2
unnamed: DUAL_JACK_8.SIG-R, R31.2
unnamed: D16.A, R32.2
unnamed: D15.A, R29.2
unnamed: DUAL_JACK_8.SIG-L, R30.2
unnamed: DUAL_JACK_9.SIG-R, R35.2
unnamed: D18.A, R36.2
unnamed: D17.A, R33.2
unnamed: DUAL_JACK_9.SIG-L, R34.2
unnamed: DUAL_JACK_10.SIG-R, R39.2
unnamed: D20.A, R40.2
unnamed: D19.A, R37.2
unnamed: DUAL_JACK_10.SIG-L, R38.2
unnamed: DUAL_JACK_11.SIG-R, R43.2
unnamed: D22.A, R44.2
unnamed: D21.A, R41.2
unnamed: DUAL_JACK_11.SIG-L, R42.2
unnamed: DUAL_JACK_12.SIG-R, R47.2
unnamed: D24.A, R48.2
unnamed: D23.A, R45.2
unnamed: DUAL_JACK_12.SIG-L, R46.2

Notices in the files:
parts and their libraries:
SparkFun-Capacitors: Licensing: Creative Commons ShareAlike 4.0 International - https://creativecommons.org/licenses/by-sa/4.0
